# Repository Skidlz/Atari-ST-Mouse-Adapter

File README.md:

# Atari-ST-Mouse-Adapter
An AVR based adapter allowing you to use PS2 mice with an Atari ST

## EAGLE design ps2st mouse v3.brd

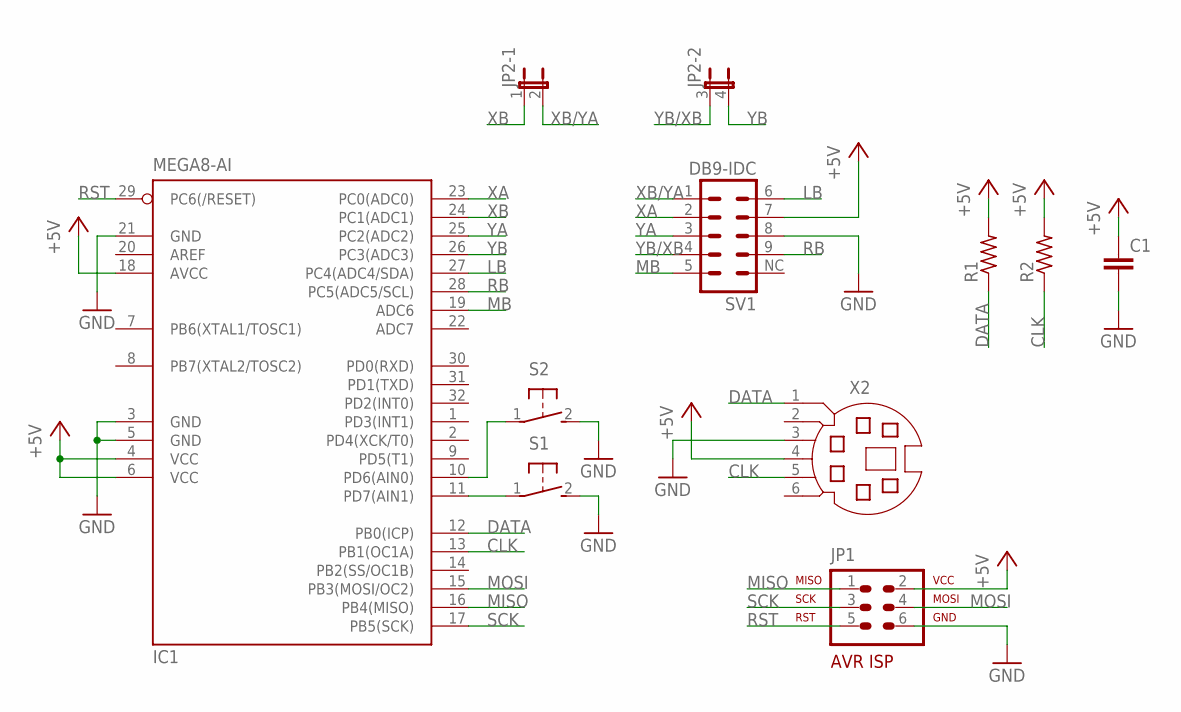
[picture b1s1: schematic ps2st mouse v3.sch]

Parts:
C1: C-EUC0805; C0805
IC1: MEGA8-AI; TQFP32-08
JP1: AVR-ISP-6VERT; AVR-ISP-6
JP2: JP2QE; JP2Q
R1, R2: R-US_R0805; R0805
S1, S2: 3X6SWITCH; 3X6
SV1: DB9-IDC; DB9
X2: MD06SS; MDIN06SS

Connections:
+5V: C1.1, IC1.4 (VCC), IC1.6 (VCC), IC1.18 (AVCC), JP1.2, R1.2, R2.2, SV1.7, X2.4
CLK: IC1.13 (PB1(OC1A)), R2.1, X2.5
DATA: IC1.12 (PB0(ICP)), R1.1, X2.1
GND: C1.2, IC1.3 (GND), IC1.5 (GND), IC1.21 (GND), JP1.6, S1.2 (S), S2.2 (S), SV1.8, X2.3
LB: IC1.27 (PC4(ADC4/SDA)), SV1.6
MB: IC1.19 (ADC6), SV1.5
MISO: IC1.16 (PB4(MISO)), JP1.1
MOSI: IC1.15 (PB3(MOSI/OC2)), JP1.4
unnamed: IC1.11 (PD7(AIN1)), S1.1
unnamed: IC1.10 (PD6(AIN0)), S2.1
RB: IC1.28 (PC5(ADC5/SCL)), SV1.9
RST: IC1.29 (PC6(/RESET)), JP1.5
SCK: IC1.17 (PB5(SCK)), JP1.3
XA: IC1.23 (PC0(ADC0)), SV1.2
XB: IC1.24 (PC1(ADC1)), JP2.1
XB/YA: JP2.2, SV1.1
YA: IC1.25 (PC2(ADC2)), SV1.3
YB: IC1.26 (PC3(ADC3)), JP2.4 (2)
YB/XB: JP2.3 (1), SV1.4

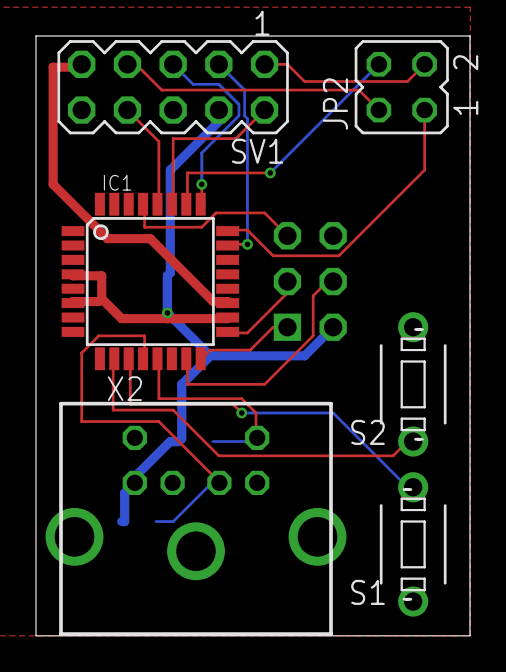
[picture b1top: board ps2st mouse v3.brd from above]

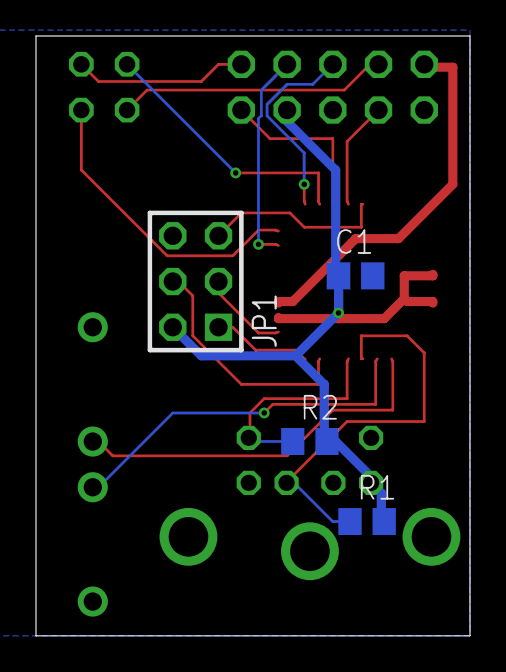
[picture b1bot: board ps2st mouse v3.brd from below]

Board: 2 copper layers, 24.1 x 33.3 mm, 10 parts (4 on the bottom side), 19 nets.

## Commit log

2021-01-20 Added schematics
